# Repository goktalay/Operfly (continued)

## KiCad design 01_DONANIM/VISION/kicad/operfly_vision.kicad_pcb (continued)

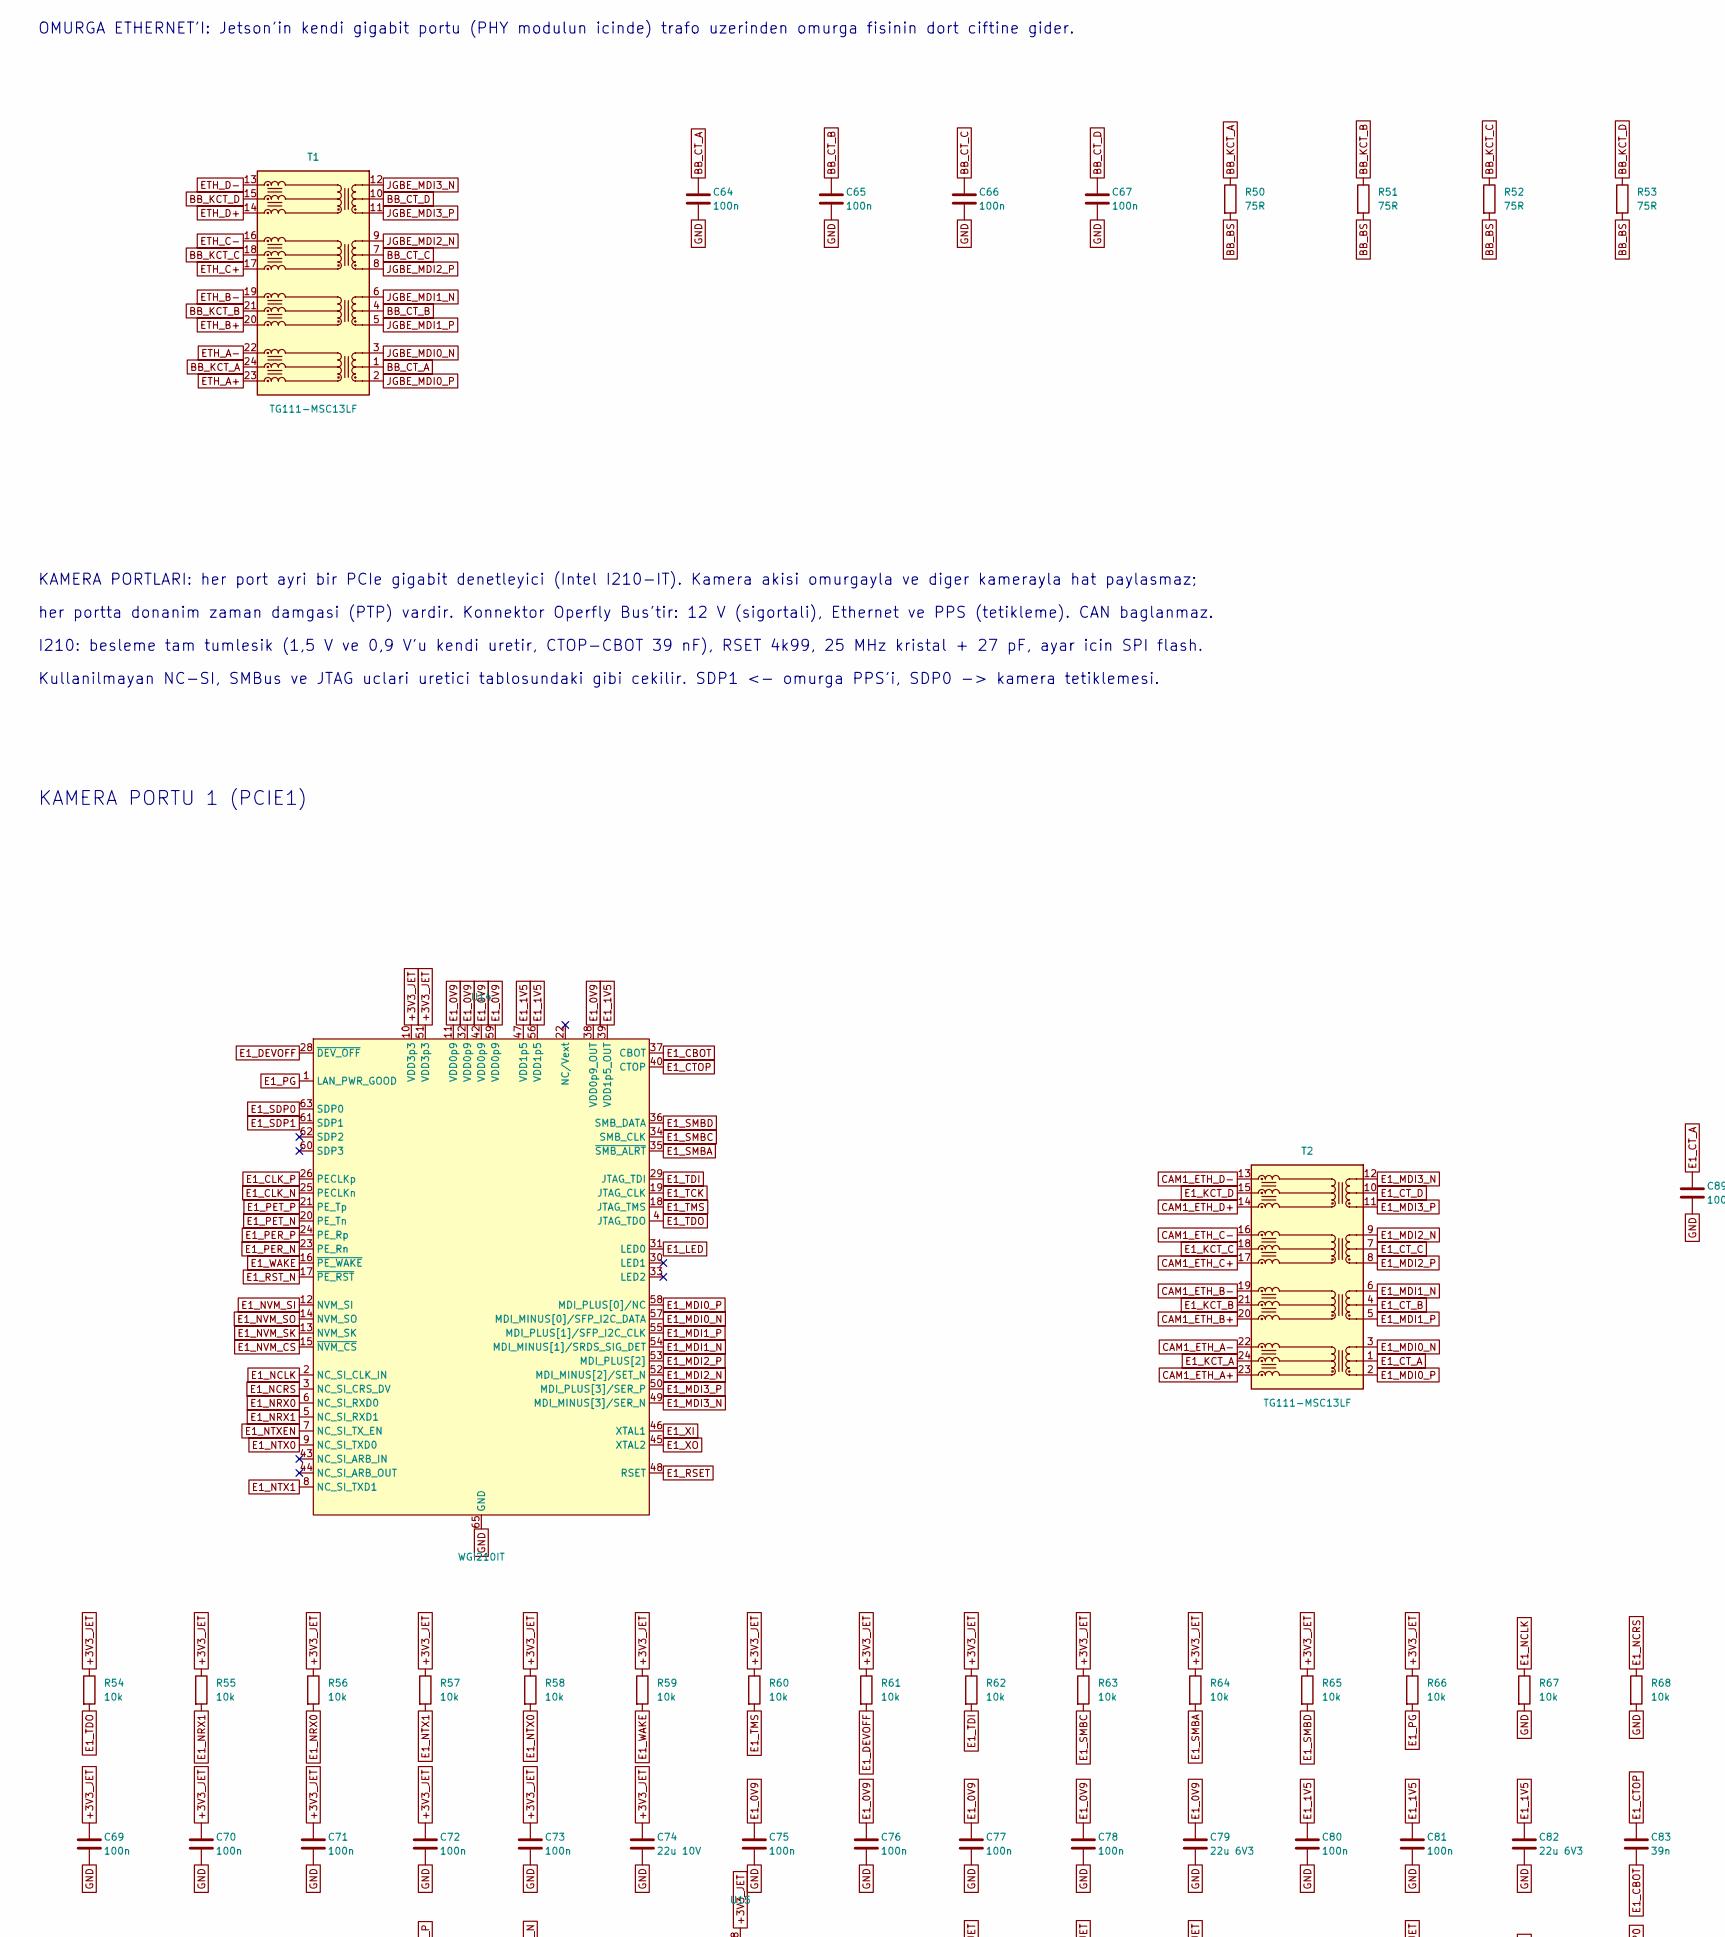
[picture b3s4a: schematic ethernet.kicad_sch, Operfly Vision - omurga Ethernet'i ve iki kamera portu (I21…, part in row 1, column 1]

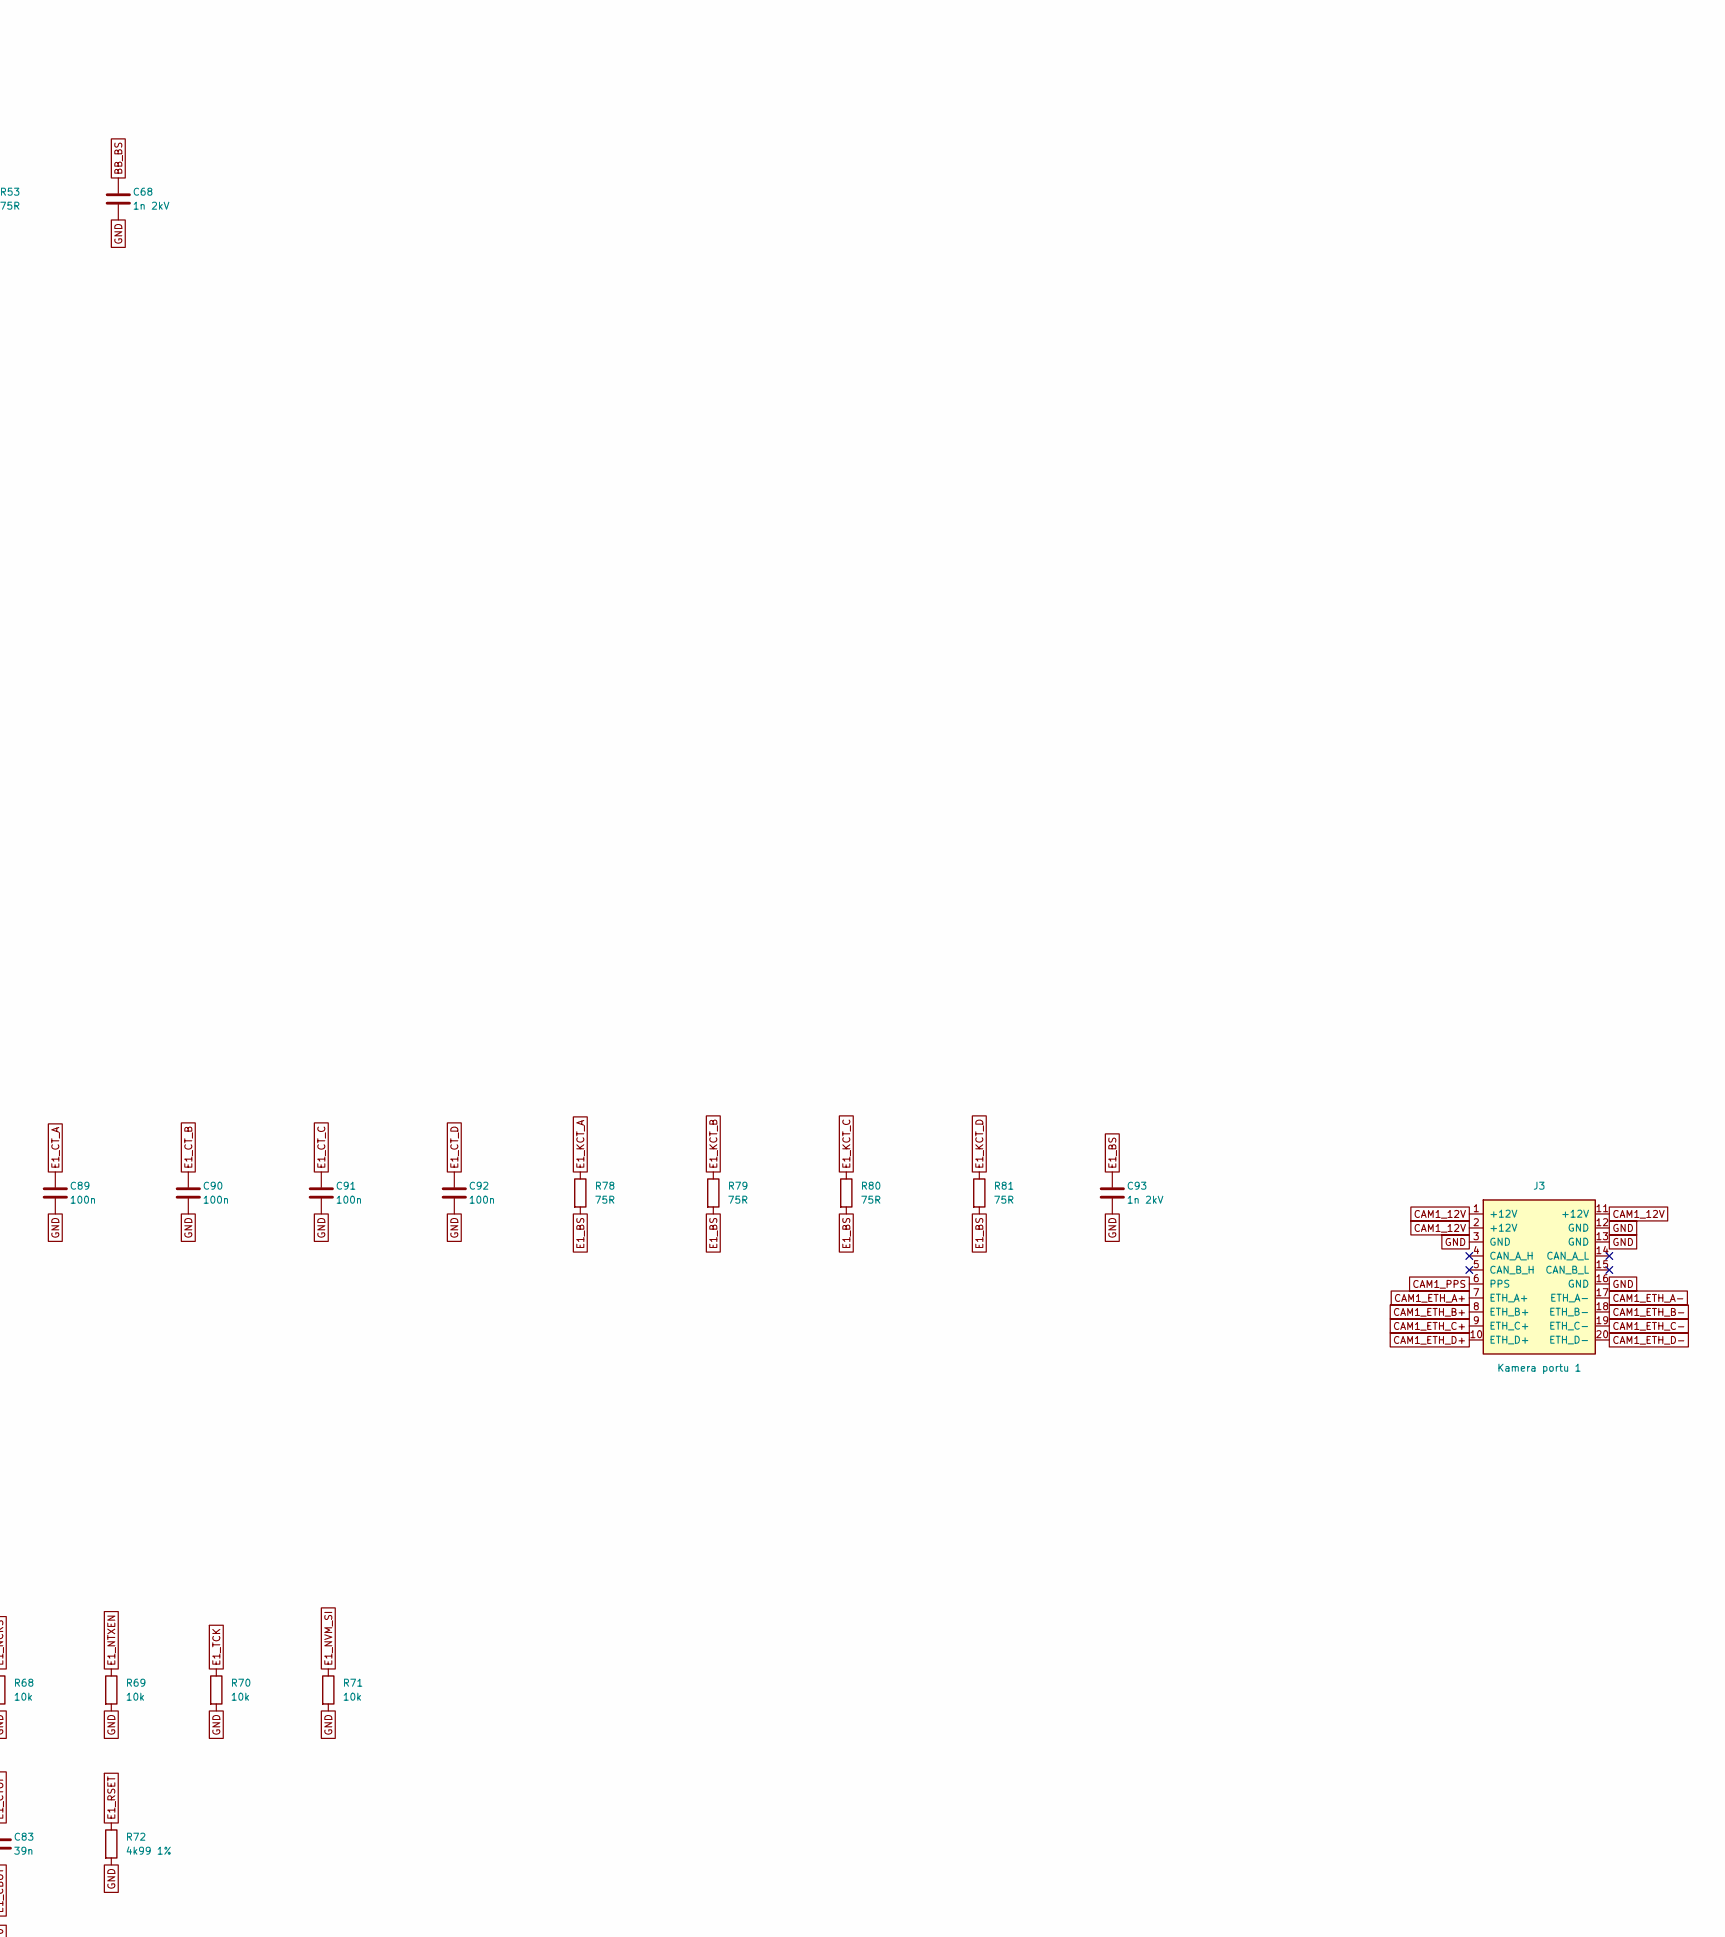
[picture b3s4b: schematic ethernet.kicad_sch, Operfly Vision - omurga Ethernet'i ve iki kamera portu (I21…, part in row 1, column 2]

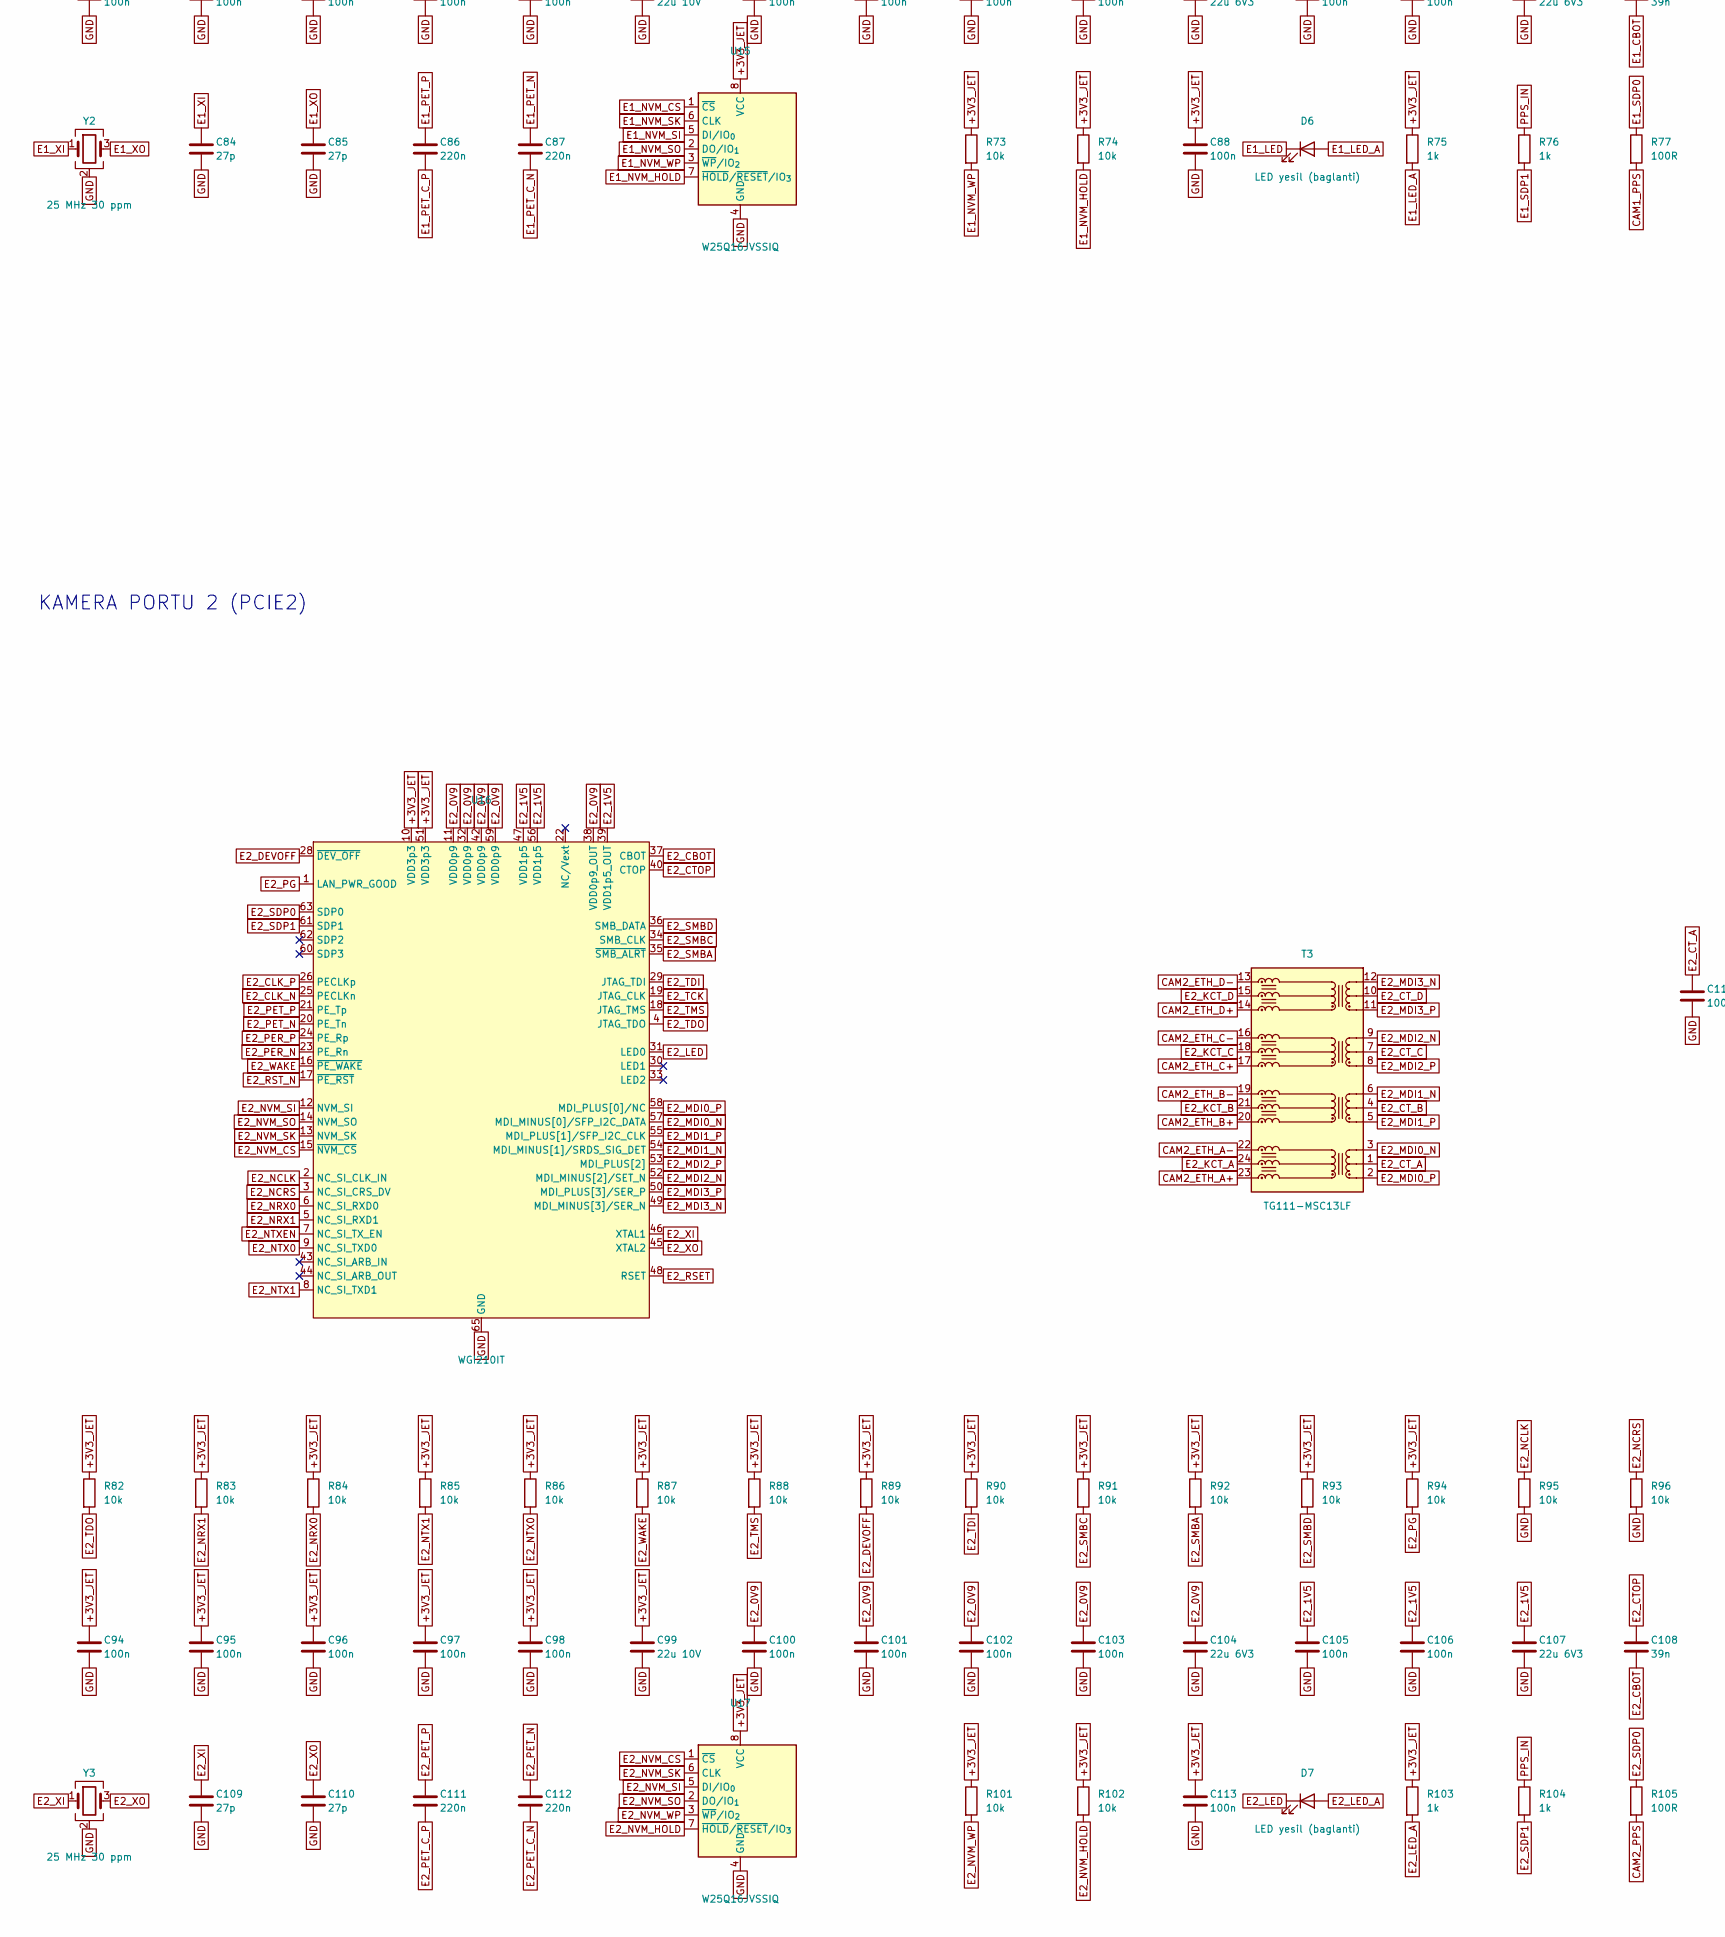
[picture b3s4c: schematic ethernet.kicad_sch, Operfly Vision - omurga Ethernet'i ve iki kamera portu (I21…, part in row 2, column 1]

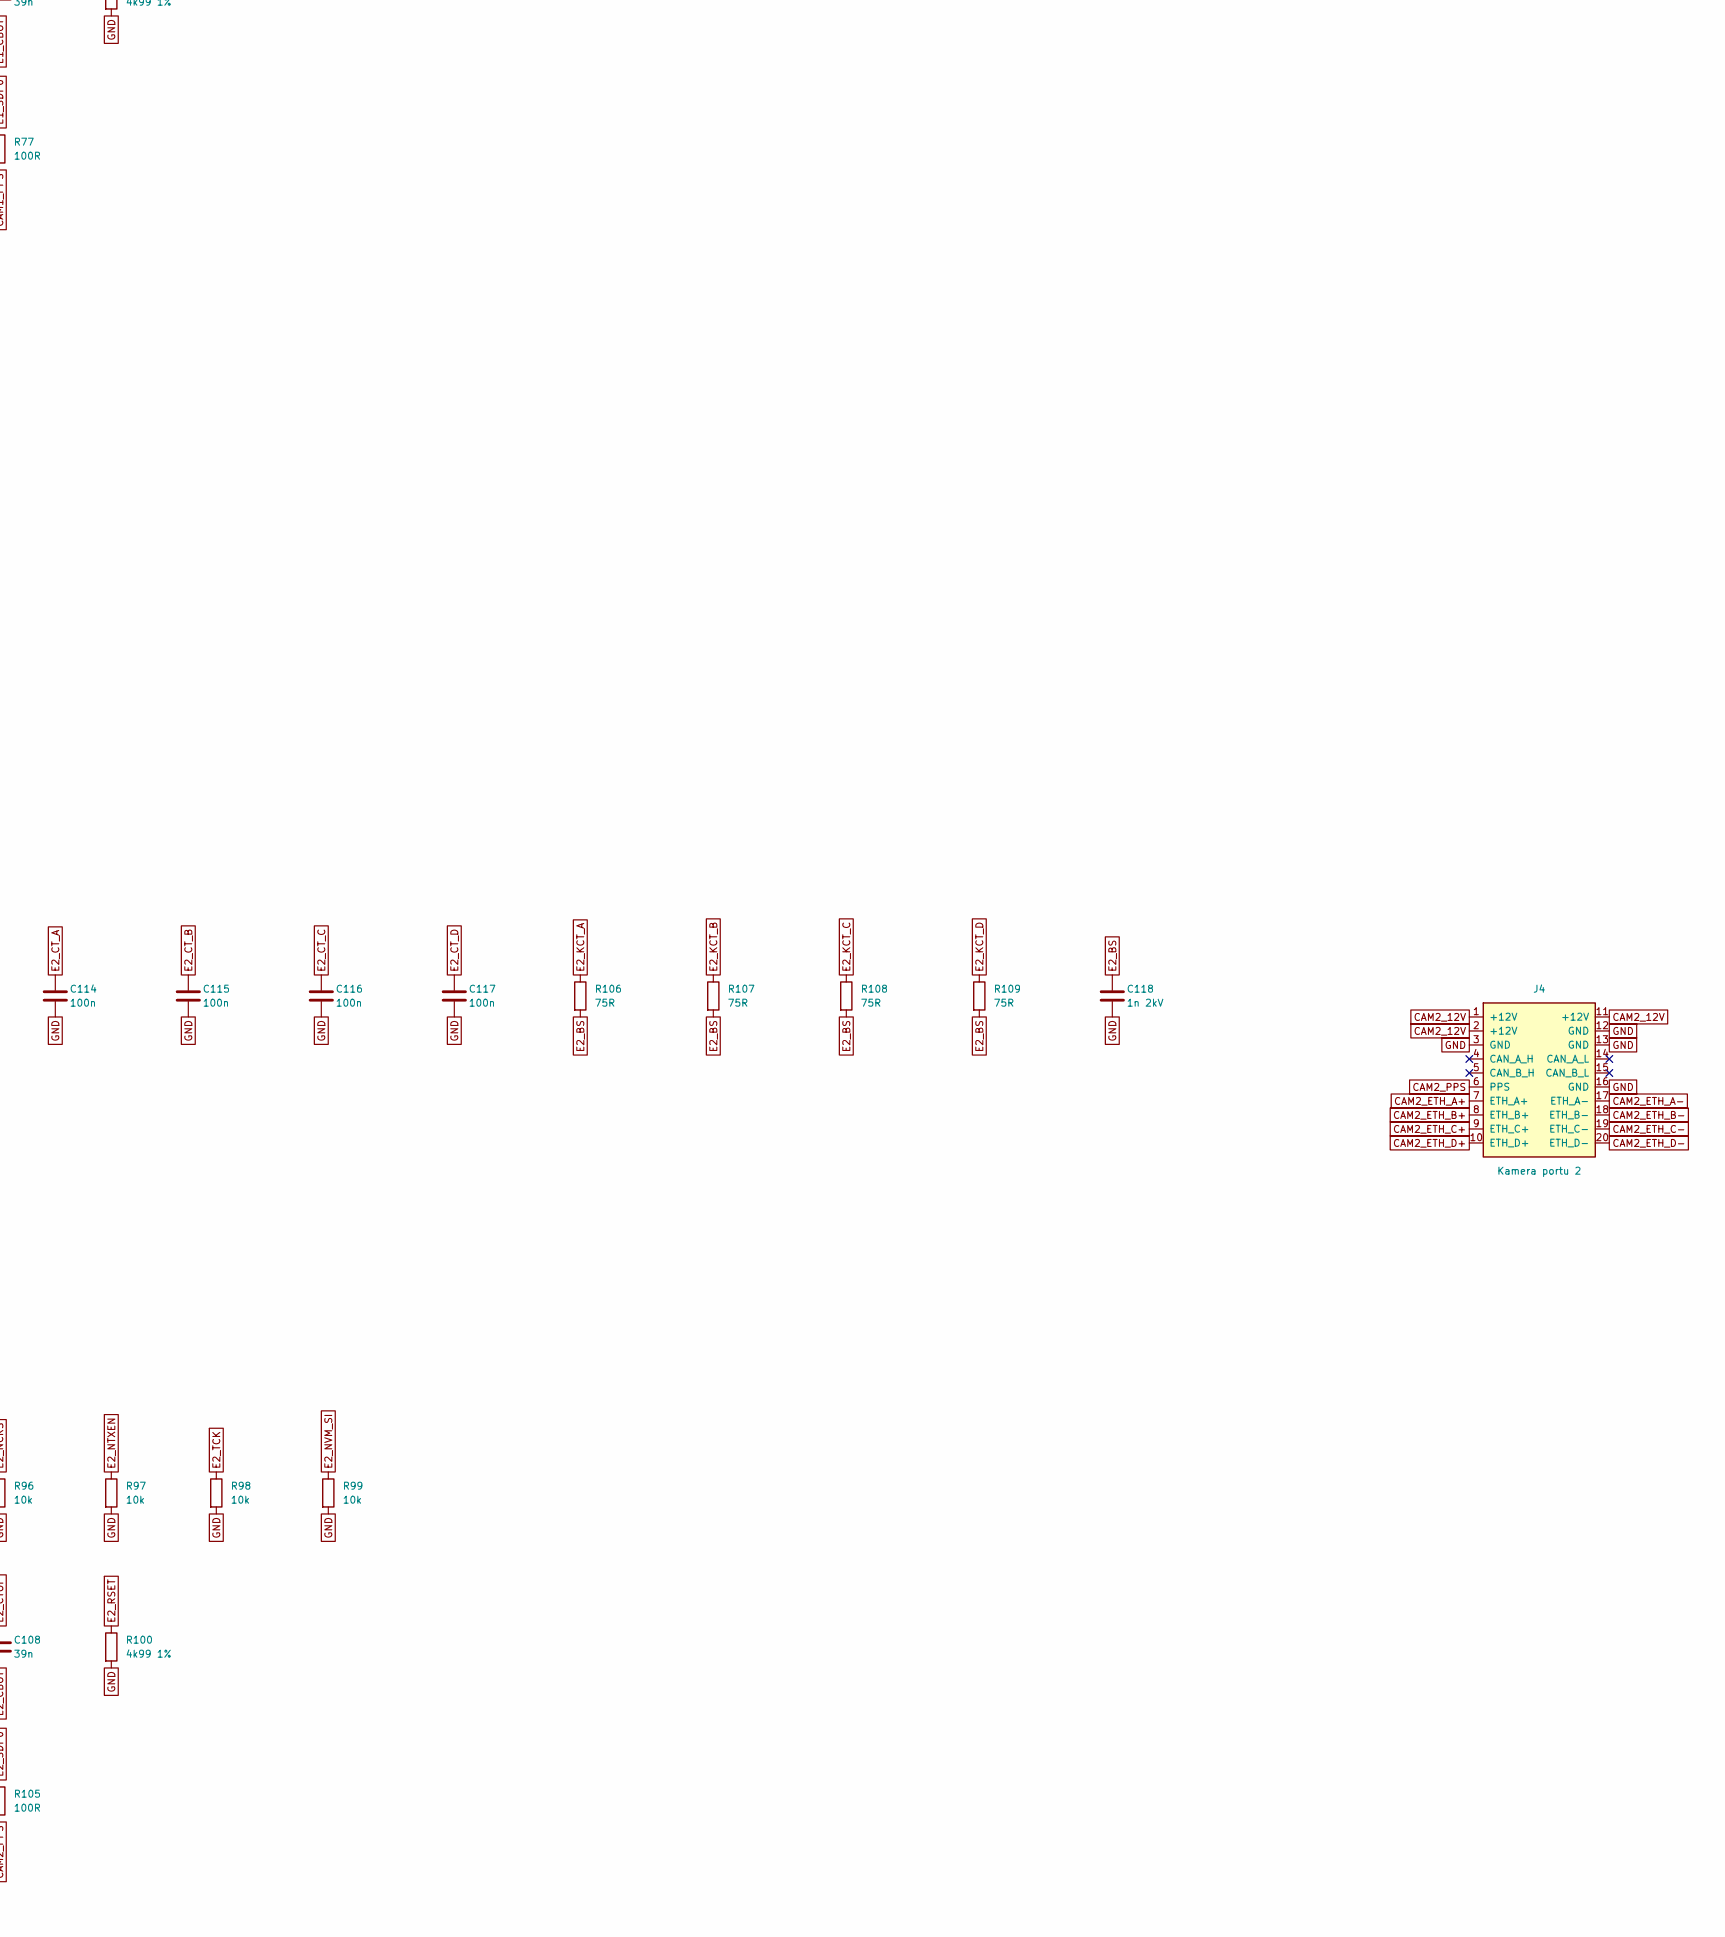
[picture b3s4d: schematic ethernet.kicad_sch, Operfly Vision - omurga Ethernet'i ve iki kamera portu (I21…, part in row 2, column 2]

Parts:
C64, C65, C66, C67, C69, C70, C71, C72, C73, C75, C76, C77, C78, C80, C81, C88, C89, C90, C91, C92, C94, C95, C96, C97, C98, C100, C101, C102, C103, C105, C106, C113, C114, C115, C116, C117: 100n; C_0402_1005Metric
C68, C93, C118: 1n 2kV; C_1206_3216Metric
C74, C99: 22u 10V; C_1206_3216Metric
C79, C82, C104, C107: 22u 6V3; C_0805_2012Metric
C83, C108: 39n; C_0402_1005Metric
C84, C85, C109, C110: 27p; C_0402_1005Metric
C86, C87, C111, C112: 220n; C_0402_1005Metric
D6, D7: LED yesil (baglanti); LED_0603_1608Metric
J3: Kamera portu 1; Harwin_Gecko_G125-MS12005M2P_2x10_P1.25mm_Vertical
J4: Kamera portu 2; Harwin_Gecko_G125-MS12005M2P_2x10_P1.25mm_Vertical
R50, R51, R52, R53, R78, R79, R80, R81, R106, R107, R108, R109: 75R; R_0402_1005Metric
R54, R55, R56, R57, R58, R59, R60, R61, R62, R63, R64, R65, R66, R67, R68, R69, R70, R71, R73, R74, R82, R83, R84, R85, R86, R87, R88, R89, R90, R91, R92, R93, R94, R95, R96, R97, R98, R99, R101, R102: 10k; R_0402_1005Metric
R72, R100: 4k99 1%; R_0402_1005Metric
R75, R76, R103, R104: 1k; R_0402_1005Metric
R77, R105: 100R; R_0402_1005Metric
T1, T2, T3: TG111-MSC13LF; Transformer_Ethernet_HALO_TG111-MSC13
U14, U16: WGI210IT; QFN-64-1EP_9x9mm_P0.5mm_EP4.7x4.7mm
U15, U17: W25Q16JVSSIQ; SOIC-8_5.3x5.3mm_P1.27mm
Y2, Y3: 25 MHz 30 ppm; Crystal_SMD_3225-4Pin_3.2x2.5mm

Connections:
+3V3_JET: C69.1, C70.1, C71.1, C72.1, C73.1, C74.1, C88.1, C94.1, C95.1, C96.1, C97.1, C98.1, C99.1, C113.1, R54.1, R55.1, R56.1, R57.1, R58.1, R59.1, R60.1, R61.1, R62.1, R63.1, R64.1, R65.1, R66.1, R73.1, R74.1, R75.1, R82.1, R83.1, R84.1, R85.1, R86.1, R87.1, R88.1, R89.1, R90.1, R91.1, R92.1, R93.1, R94.1, R101.1, R102.1, R103.1, U14.10 (VDD3p3), U14.27 (VDD3p3), U14.41 (VDD3p3), U14.51 (VDD3p3), U14.64 (VDD3p3), U15.8 (VCC), U16.10 (VDD3p3), U16.27 (VDD3p3), U16.41 (VDD3p3), U16.51 (VDD3p3), U16.64 (VDD3p3), U17.8 (VCC); also elsewhere on the board
BB_BS: C68.1, R50.2, R51.2, R52.2, R53.2
BB_CT_A: C64.1, T1.1 (TCT1)
BB_CT_B: C65.1, T1.4 (TCT2)
BB_CT_C: C66.1, T1.7 (TCT3)
BB_CT_D: C67.1, T1.10 (TCT4)
BB_KCT_A: R50.1, T1.24 (MTC1)
BB_KCT_B: R51.1, T1.21 (MCT2)
BB_KCT_C: R52.1, T1.18 (MCT3)
BB_KCT_D: R53.1, T1.15 (MCT4)
CAM1_12V: J3.1 (+12V), J3.2 (+12V), J3.11 (+12V); also elsewhere on the board
CAM1_ETH_A+: J3.7 (ETH_A+), T2.23 (MTX1+)
CAM1_ETH_A-: J3.17 (ETH_A-), T2.22 (MTX1-)
CAM1_ETH_B+: J3.8 (ETH_B+), T2.20 (MTX2+)
CAM1_ETH_B-: J3.18 (ETH_B-), T2.19 (MTX2-)
CAM1_ETH_C+: J3.9 (ETH_C+), T2.17 (MTX3+)
CAM1_ETH_C-: J3.19 (ETH_C-), T2.16 (MTX3-)
CAM1_ETH_D+: J3.10 (ETH_D+), T2.14 (MX4+)
CAM1_ETH_D-: J3.20 (ETH_D-), T2.13 (MX4-)
CAM1_PPS: J3.6 (PPS), R77.2
CAM2_12V: J4.1 (+12V), J4.2 (+12V), J4.11 (+12V); also elsewhere on the board
CAM2_ETH_A+: J4.7 (ETH_A+), T3.23 (MTX1+)
CAM2_ETH_A-: J4.17 (ETH_A-), T3.22 (MTX1-)
CAM2_ETH_B+: J4.8 (ETH_B+), T3.20 (MTX2+)
CAM2_ETH_B-: J4.18 (ETH_B-), T3.19 (MTX2-)
CAM2_ETH_C+: J4.9 (ETH_C+), T3.17 (MTX3+)
CAM2_ETH_C-: J4.19 (ETH_C-), T3.16 (MTX3-)
CAM2_ETH_D+: J4.10 (ETH_D+), T3.14 (MX4+)
CAM2_ETH_D-: J4.20 (ETH_D-), T3.13 (MX4-)
CAM2_PPS: J4.6 (PPS), R105.2
E1_0V9: C75.1, C76.1, C77.1, C78.1, C79.1, U14.11 (VDD0p9), U14.32 (VDD0p9), U14.38 (VDD0p9_OUT), U14.42 (VDD0p9), U14.59 (VDD0p9)
E1_1V5: C80.1, C81.1, C82.1, U14.39 (VDD1p5_OUT), U14.47 (VDD1p5), U14.56 (VDD1p5)
E1_BS: C93.1, R78.2, R79.2, R80.2, R81.2
E1_CBOT: C83.2, U14.37 (CBOT)
E1_CLK_N: U14.25 (PECLKn); also elsewhere on the board
E1_CLK_P: U14.26 (PECLKp); also elsewhere on the board
E1_CTOP: C83.1, U14.40 (CTOP)
E1_CT_A: C89.1, T2.1 (TCT1)
E1_CT_B: C90.1, T2.4 (TCT2)
E1_CT_C: C91.1, T2.7 (TCT3)
E1_CT_D: C92.1, T2.10 (TCT4)
E1_DEVOFF: R61.2, U14.28 (~DEV_OFF)
E1_KCT_A: R78.1, T2.24 (MTC1)
E1_KCT_B: R79.1, T2.21 (MCT2)
E1_KCT_C: R80.1, T2.18 (MCT3)
E1_KCT_D: R81.1, T2.15 (MCT4)
E1_LED: D6.1 (K), U14.31 (LED0)
E1_LED_A: D6.2 (A), R75.2
E1_MDI0_N: T2.3 (TD1-), U14.57 (MDI_MINUS[0]/SFP_I2C_DATA)
E1_MDI0_P: T2.2 (TD1+), U14.58 (MDI_PLUS[0]/NC)
E1_MDI1_N: T2.6 (TD2-), U14.54 (MDI_MINUS[1]/SRDS_SIG_DET)
E1_MDI1_P: T2.5 (TD2+), U14.55 (MDI_PLUS[1]/SFP_I2C_CLK)
E1_MDI2_N: T2.9 (TD3-), U14.52 (MDI_MINUS[2]/SET_N)
E1_MDI2_P: T2.8 (TD3+), U14.53 (MDI_PLUS[2])
E1_MDI3_N: T2.12 (TD4-), U14.49 (MDI_MINUS[3]/SER_N)
E1_MDI3_P: T2.11 (TD4+), U14.50 (MDI_PLUS[3]/SER_P)
E1_NCLK: R67.1, U14.2 (NC_SI_CLK_IN)
E1_NCRS: R68.1, U14.3 (NC_SI_CRS_DV)
E1_NRX0: R56.2, U14.6 (NC_SI_RXD0)
E1_NRX1: R55.2, U14.5 (NC_SI_RXD1)
E1_NTX0: R58.2, U14.9 (NC_SI_TXD0)
E1_NTX1: R57.2, U14.8 (NC_SI_TXD1)
E1_NTXEN: R69.1, U14.7 (NC_SI_TX_EN)
E1_NVM_CS: U14.15 (~NVM_CS), U15.1 (~CS)
E1_NVM_HOLD: R74.2, U15.7 (~HOLD/~RESET/IO_{3})
E1_NVM_SI: R71.1, U14.12 (NVM_SI), U15.5 (DI/IO_{0})
E1_NVM_SK: U14.13 (NVM_SK), U15.6 (CLK)
E1_NVM_SO: U14.14 (NVM_SO), U15.2 (DO/IO_{1})
E1_NVM_WP: R73.2, U15.3 (~WP/IO_{2})
E1_PER_N: U14.23 (PE_Rn); also elsewhere on the board
E1_PER_P: U14.24 (PE_Rp); also elsewhere on the board
E1_PET_C_N: C87.2; also elsewhere on the board
E1_PET_C_P: C86.2; also elsewhere on the board
E1_PET_N: C87.1, U14.20 (PE_Tn)
E1_PET_P: C86.1, U14.21 (PE_Tp)
E1_PG: R66.2, U14.1 (LAN_PWR_GOOD)
E1_RSET: R72.1, U14.48 (RSET)
E1_RST_N: U14.17 (~PE_RST); also elsewhere on the board
E1_SDP0: R77.1, U14.63 (SDP0)
E1_SDP1: R76.2, U14.61 (SDP1)
E1_SMBA: R64.2, U14.35 (~SMB_ALRT)
E1_SMBC: R63.2, U14.34 (SMB_CLK)
E1_SMBD: R65.2, U14.36 (SMB_DATA)
E1_TCK: R70.1, U14.19 (JTAG_CLK)
E1_TDI: R62.2, U14.29 (JTAG_TDI)
E1_TDO: R54.2, U14.4 (JTAG_TDO)
E1_TMS: R60.2, U14.18 (JTAG_TMS)
E1_WAKE: R59.2, U14.16 (~PE_WAKE)
E1_XI: C84.1, U14.46 (XTAL1), Y2.1
E1_XO: C85.1, U14.45 (XTAL2), Y2.3
E2_0V9: C100.1, C101.1, C102.1, C103.1, C104.1, U16.11 (VDD0p9), U16.32 (VDD0p9), U16.38 (VDD0p9_OUT), U16.42 (VDD0p9), U16.59 (VDD0p9)
E2_1V5: C105.1, C106.1, C107.1, U16.39 (VDD1p5_OUT), U16.47 (VDD1p5), U16.56 (VDD1p5)
E2_BS: C118.1, R106.2, R107.2, R108.2, R109.2
E2_CBOT: C108.2, U16.37 (CBOT)
E2_CLK_N: U16.25 (PECLKn); also elsewhere on the board
E2_CLK_P: U16.26 (PECLKp); also elsewhere on the board
E2_CTOP: C108.1, U16.40 (CTOP)
E2_CT_A: C114.1, T3.1 (TCT1)
E2_CT_B: C115.1, T3.4 (TCT2)
E2_CT_C: C116.1, T3.7 (TCT3)
E2_CT_D: C117.1, T3.10 (TCT4)
E2_DEVOFF: R89.2, U16.28 (~DEV_OFF)
E2_KCT_A: R106.1, T3.24 (MTC1)
E2_KCT_B: R107.1, T3.21 (MCT2)
E2_KCT_C: R108.1, T3.18 (MCT3)
E2_KCT_D: R109.1, T3.15 (MCT4)
E2_LED: D7.1 (K), U16.31 (LED0)
E2_LED_A: D7.2 (A), R103.2
E2_MDI0_N: T3.3 (TD1-), U16.57 (MDI_MINUS[0]/SFP_I2C_DATA)
E2_MDI0_P: T3.2 (TD1+), U16.58 (MDI_PLUS[0]/NC)
E2_MDI1_N: T3.6 (TD2-), U16.54 (MDI_MINUS[1]/SRDS_SIG_DET)
E2_MDI1_P: T3.5 (TD2+), U16.55 (MDI_PLUS[1]/SFP_I2C_CLK)
E2_MDI2_N: T3.9 (TD3-), U16.52 (MDI_MINUS[2]/SET_N)
E2_MDI2_P: T3.8 (TD3+), U16.53 (MDI_PLUS[2])
E2_MDI3_N: T3.12 (TD4-), U16.49 (MDI_MINUS[3]/SER_N)
E2_MDI3_P: T3.11 (TD4+), U16.50 (MDI_PLUS[3]/SER_P)
E2_NCLK: R95.1, U16.2 (NC_SI_CLK_IN)
E2_NCRS: R96.1, U16.3 (NC_SI_CRS_DV)
E2_NRX0: R84.2, U16.6 (NC_SI_RXD0)
E2_NRX1: R83.2, U16.5 (NC_SI_RXD1)
E2_NTX0: R86.2, U16.9 (NC_SI_TXD0)
E2_NTX1: R85.2, U16.8 (NC_SI_TXD1)
E2_NTXEN: R97.1, U16.7 (NC_SI_TX_EN)
E2_NVM_CS: U16.15 (~NVM_CS), U17.1 (~CS)
E2_NVM_HOLD: R102.2, U17.7 (~HOLD/~RESET/IO_{3})
E2_NVM_SI: R99.1, U16.12 (NVM_SI), U17.5 (DI/IO_{0})
E2_NVM_SK: U16.13 (NVM_SK), U17.6 (CLK)
E2_NVM_SO: U16.14 (NVM_SO), U17.2 (DO/IO_{1})
E2_NVM_WP: R101.2, U17.3 (~WP/IO_{2})
E2_PER_N: U16.23 (PE_Rn); also elsewhere on the board
E2_PER_P: U16.24 (PE_Rp); also elsewhere on the board
E2_PET_C_N: C112.2; also elsewhere on the board
E2_PET_C_P: C111.2; also elsewhere on the board
E2_PET_N: C112.1, U16.20 (PE_Tn)
E2_PET_P: C111.1, U16.21 (PE_Tp)
E2_PG: R94.2, U16.1 (LAN_PWR_GOOD)
E2_RSET: R100.1, U16.48 (RSET)
E2_RST_N: U16.17 (~PE_RST); also elsewhere on the board
E2_SDP0: R105.1, U16.63 (SDP0)
E2_SDP1: R104.2, U16.61 (SDP1)
E2_SMBA: R92.2, U16.35 (~SMB_ALRT)
E2_SMBC: R91.2, U16.34 (SMB_CLK)
E2_SMBD: R93.2, U16.36 (SMB_DATA)
E2_TCK: R98.1, U16.19 (JTAG_CLK)
E2_TDI: R90.2, U16.29 (JTAG_TDI)
E2_TDO: R82.2, U16.4 (JTAG_TDO)
E2_TMS: R88.2, U16.18 (JTAG_TMS)
E2_WAKE: R87.2, U16.16 (~PE_WAKE)
E2_XI: C109.1, U16.46 (XTAL1), Y3.1
E2_XO: C110.1, U16.45 (XTAL2), Y3.3
ETH_A+: T1.23 (MTX1+); also elsewhere on the board
ETH_A-: T1.22 (MTX1-); also elsewhere on the board
ETH_B+: T1.20 (MTX2+); also elsewhere on the board
ETH_B-: T1.19 (MTX2-); also elsewhere on the board
ETH_C+: T1.17 (MTX3+); also elsewhere on the board
ETH_C-: T1.16 (MTX3-); also elsewhere on the board
ETH_D+: T1.14 (MX4+); also elsewhere on the board
ETH_D-: T1.13 (MX4-); also elsewhere on the board
GND: C64.2, C65.2, C66.2, C67.2, C68.2, C69.2, C70.2, C71.2, C72.2, C73.2, C74.2, C75.2, C76.2, C77.2, C78.2, C79.2, C80.2, C81.2, C82.2, C84.2, C85.2, C88.2, C89.2, C90.2, C91.2, C92.2, C93.2, C94.2, C95.2, C96.2, C97.2, C98.2, C99.2, C100.2, C101.2, C102.2, C103.2, C104.2, C105.2, C106.2, C107.2, C109.2, C110.2, C113.2, C114.2, C115.2, C116.2, C117.2, C118.2, J3.3 (GND), J3.12 (GND), J3.13 (GND), J3.16 (GND), J4.3 (GND), J4.12 (GND), J4.13 (GND), J4.16 (GND), R67.2, R68.2, R69.2, R70.2, R71.2, R72.2, R95.2, R96.2, R97.2, R98.2, R99.2, R100.2, U14.65 (GND), U15.4 (GND), U16.65 (GND), U17.4 (GND), Y2.2 (G), Y2.4 (G), Y3.2 (G), Y3.4 (G); also elsewhere on the board
JGBE_MDI0_N: T1.3 (TD1-); also elsewhere on the board
JGBE_MDI0_P: T1.2 (TD1+); also elsewhere on the board
JGBE_MDI1_N: T1.6 (TD2-); also elsewhere on the board
JGBE_MDI1_P: T1.5 (TD2+); also elsewhere on the board
JGBE_MDI2_N: T1.9 (TD3-); also elsewhere on the board
JGBE_MDI2_P: T1.8 (TD3+); also elsewhere on the board
JGBE_MDI3_N: T1.12 (TD4-); also elsewhere on the board
JGBE_MDI3_P: T1.11 (TD4+); also elsewhere on the board
PPS_IN: R76.1, R104.1; also elsewhere on the board

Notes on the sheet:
I210: besleme tam tumlesik (1,5 V ve 0,9 V'u kendi uretir, CTOP-CBOT 39 nF), RSET 4k99, 25 MHz kristal + 27 pF, ayar icin SPI flash.
Kullanilmayan NC-SI, SMBus ve JTAG uclari uretici tablosundaki gibi cekilir. SDP1 <- omurga PPS'i, SDP0 -> kamera tetiklemesi.
KAMERA PORTLARI: her port ayri bir PCIe gigabit denetleyici (Intel I210-IT). Kamera akisi omurgayla ve diger kamerayla hat paylasmaz;
KAMERA PORTU 1 (PCIE1)
KAMERA PORTU 2 (PCIE2)
her portta donanim zaman damgasi (PTP) vardir. Konnektor Operfly Bus'tir: 12 V (sigortali), Ethernet ve PPS (tetikleme). CAN baglanmaz.
OMURGA ETHERNET'I: Jetson'in kendi gigabit portu (PHY modulun icinde) trafo uzerinden omurga fisinin dort ciftine gider.

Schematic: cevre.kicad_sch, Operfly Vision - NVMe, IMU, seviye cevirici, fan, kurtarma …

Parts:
C119, C120: 22u 10V; C_1206_3216Metric
C121, C122, C123, C124, C125, C127, C128: 100n; C_0402_1005Metric
C126: 2u2; C_0603_1608Metric
C129: 1n; C_0402_1005Metric
C130: 10u 10V; C_0805_2012Metric
C131: 1u 25V; C_0603_1608Metric
D8: USBLC6-2P6; SOT-666
J5: M.2 Key M (NVMe 2242/2280); TE_M.2_M_2x38-1MP_P0.5mm
J6: Fan (PicoBlade); Molex_PicoBlade_53047-0410_1x04_P1.25mm_Vertical
J7: USB Type-C (kurtarma); USB_C_Receptacle_GCT_USB4105-xx-A_16P_TopMnt_Horizontal
Q4: 2N7002; SOT-23
R110, R112, R113, R114: 10k; R_0402_1005Metric
R111: 100R; R_0402_1005Metric
R115, R116: 5k1 1%; R_0402_1005Metric
R117, R118: 100k; R_0402_1005Metric
U18: ICM-42688-P; Bosch_LGA-14_3x2.5mm_P0.5mm
U19: TXS0104EPW; TSSOP-14_4.4x5mm_P0.65mm

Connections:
+1V8_JET: C124.1, C125.1, C126.1, C127.1, U18.5 (VDDIO), U18.8 (VDD), U19.1 (V_{CCA}), U19.8 (OE); also elsewhere on the board
+3V3: C128.1, R113.1, U19.14 (V_{CCB}); also elsewhere on the board
+3V3_M2: C119.1, C120.1, C121.1, C122.1, C123.1, J5.2 (3.3V), J5.4 (3.3V), J5.12 (3.3V), J5.14 (3.3V), J5.16 (3.3V), J5.18 (3.3V), J5.70 (3.3V), J5.72 (3.3V), J5.74 (3.3V); also elsewhere on the board
+5V: C130.1, J6.2; also elsewhere on the board
FAN_PWM: J6.4, R111.2, R112.1
FAN_PWM_3V3: R111.1, U19.10 (B4)
FAN_TACH: C129.1, R113.2, R114.2; also elsewhere on the board
FAN_TACH_K: J6.3, R114.1
GND: C119.2, C120.2, C121.2, C122.2, C123.2, C124.2, C125.2, C126.2, C127.2, C128.2, C129.2, C130.2, C131.2, D8.2 (GND), J5.1 (GND), J5.3 (GND), J5.9 (GND), J5.15 (GND), J5.21 (GND), J5.27 (GND), J5.33 (GND), J5.39 (GND), J5.45 (GND), J5.51 (GND), J5.57 (GND), J5.71 (GND), J5.73 (GND), J5.75 (GND), J6.1, J7.A1 (GND), J7.A12 (GND), J7.B1 (GND), J7.B12 (GND), J7.SH (SHIELD), Q4.2 (S), R110.2, R112.2, R115.2, R116.2, R118.2, U18.6 (GND), U18.7 (RESV7), U18.11 (RESV11), U19.7 (GND); also elsewhere on the board
IMU_CS_N: U18.12 (AP_CS); also elsewhere on the board
IMU_INT: U18.4 (INT1); also elsewhere on the board
IMU_MISO: U18.1 (AP_SDO); also elsewhere on the board
IMU_MOSI: U18.14 (AP_SDI); also elsewhere on the board
IMU_SCK: U18.13 (AP_SCLK); also elsewhere on the board
JET_FAN_PWM_1V8: U19.5 (A4); also elsewhere on the board
JET_PPS_1V8: U19.4 (A3); also elsewhere on the board
JET_UART_RX_1V8: U19.3 (A2); also elsewhere on the board
JET_UART_TX_1V8: U19.2 (A1); also elsewhere on the board
M2_CLKREQ_N: J5.52 (~CLKREQ); also elsewhere on the board
M2_CLK_N: J5.53 (REFCLKn); also elsewhere on the board
M2_CLK_P: J5.55 (REFCLKp); also elsewhere on the board
M2_DEVSLP: J5.38 (DEVSLP), R110.1
M2_PER0_N: J5.41 (PERn0/SATA-B+); also elsewhere on the board
M2_PER0_P: J5.43 (PERp0/SATA-B-); also elsewhere on the board
M2_PER1_N: J5.29 (PERn1); also elsewhere on the board
M2_PER1_P: J5.31 (PERp1); also elsewhere on the board
M2_PER2_N: J5.17 (PERn2); also elsewhere on the board
M2_PER2_P: J5.19 (PERp2); also elsewhere on the board
M2_PER3_N: J5.5 (PERn3); also elsewhere on the board
M2_PER3_P: J5.7 (PERp3); also elsewhere on the board
M2_PET0_N: J5.47 (PETn0/SATA-A-); also elsewhere on the board
M2_PET0_P: J5.49 (PETp0/SATA-A+); also elsewhere on the board
M2_PET1_N: J5.35 (PETn1); also elsewhere on the board
M2_PET1_P: J5.37 (PETp1); also elsewhere on the board
M2_PET2_N: J5.23 (PETn2); also elsewhere on the board
M2_PET2_P: J5.25 (PETp2); also elsewhere on the board
M2_PET3_N: J5.11 (PETn3); also elsewhere on the board
M2_PET3_P: J5.13 (PETp3); also elsewhere on the board
M2_RST_N: J5.50 (~PERST); also elsewhere on the board
MCU_RX: U19.13 (B1); also elsewhere on the board
MCU_TX: U19.12 (B2); also elsewhere on the board
PCIE_WAKE_N: J5.54 (~PEWAKE); also elsewhere on the board
PPS_IN: U19.11 (B3); also elsewhere on the board
USB0_DM: D8.3 (I/O2), D8.4 (I/O2), J7.A7 (D-), J7.B7 (D-); also elsewhere on the board
USB0_DP: D8.1 (I/O1), D8.6 (I/O1), J7.A6 (D+), J7.B6 (D+); also elsewhere on the board
USB0_VBUS_DET_N: Q4.3 (D); also elsewhere on the board
USB_CC1: J7.A5 (CC1), R115.1
USB_CC2: J7.B5 (CC2), R116.1
USB_VBUS: C131.1, D8.5 (VBUS), J7.A4 (VBUS), J7.A9 (VBUS), J7.B4 (VBUS), J7.B9 (VBUS), R117.1
USB_VBUS_G: Q4.1 (G), R117.2, R118.1

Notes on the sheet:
FAN (5 V, 4 uclu: GND, +5V, devir, PWM): PWM Jetson'dan; Jetson kapaliyken 10k asagi cekme fani durdurur. Devir darbesi islemciye.
IMU (ICM-42688-P, Jetson SPI0, 1,8 V): goruntu ile atalet olcumunu ayni saatle eslemek icin karta ozel IMU. INT1 -> GPIO09.
transistor GPIO00'i dusuge ceker (bilgisayar bagli). CC uclarinda 5k1: kart tuketicidir. VBUS karti beslemez.
SEVIYE CEVIRICI (TXS0104E, 1,8 V <-> 3,3 V): Jetson UART1 <-> dugum islemcisi, omurga PPS'i -> GPIO07, fan PWM (GPIO14).
PET uclari Jetson'in verici ciftlerine 220 nF uzerinden (Jetson sayfasinda) baglanir.
KURTARMA / YAZILIM YUKLEME USB'si (Type-C, Jetson USB0, aygit kipi): Jetson'a ilk yazilim bu porttan yuklenir. VBUS gelince
M.2 NVMe (Key M, PCIE0, dort serit): 3,3 V ayri regulatorden. Soketin PER uclari Jetson'in alici ciftlerine dogrudan,
Jetson kapaliyken (1,8 V yok) cevirici uclarini birakir; kart Jetson'a gerilim vermez.
